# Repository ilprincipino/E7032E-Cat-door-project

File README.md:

# E7032E-Cat-door-project
Universal low power antennas for pet microchips
<p>
  
**Project members:** <br>
Matilda Segerlund, matseg-9@student.ltu.se  <br>
Nebez Rashid, nabras-9@student.ltu.se <br>
Anders Hagström, hagane-9@student.ltu.se <br>
Agnes Lindsten, agelin-7@student.ltu.se <br>
Arvid Mattsson, arvmat-9@student.ltu.se <br>
Jakob Ekvall, jakekv-9@student.ltu.se <br>

Link to report: [https://www.overleaf.com/read/vsyjcxfwmcch](https://www.overleaf.com/read/vsyjcxfwmcch) <br>

Link to presentation: https://docs.google.com/presentation/d/12QPiXXhClUaFdsH-6-YMc6YWno67U1GOmlV3GwxZOh8/edit?usp=sharing

Link to WBS/project plan: https://docs.google.com/spreadsheets/d/1j_RC8x2nzi24WwkHtlm5jIMLNItzt1e427vKWdE4rbc/edit?usp=sharing <br>

**Background:** <br>
Since the mid-80's, microchip implants have been used in pets and livestocks to identify them. These implements are a little larger than a rice grain. They are passive RFID chips that must be remotely powered to receive the identification information. They are progressively been required by law. <br>

Beside legal identification, these microchips can be used to identify a pet when they want to be fed (i.e., not allow an obese pet to over eat) or to let them enter or exit their home. The latter prevents "foreign" cats to enter homes where they have no business to be in. <br>

There is a problem when the orientation of the scanner's antenna and the microchips are not aligned. The pet doors and feeders are battery powered and fixed. The former results in not enough power to retrieve the information, while the latter could have been a solution by rotating the antenna (or chip inside the pet). <br>

**Objective:** <br>
The project is simply to design a low power antenna that allows the microchip to be read whatever is its relative orientation. <br>

**Key features:** <br>
* **Compatibility:** The solution must be ISO 11784 and ISO 11785 compliant. That is, it must be able to be optimized for 134.2 kHz, but should also be able to read at 125 kHz for US microchips.
* **Low power:** The cat door should work 6 months on four AA batteries.
* **Size:** It should fit in a pet door.
* **Temperature:** It should function in temperatures from -20°C to 60°C.
* **Internet ready:** The solution should be able to integrate a secured solution that connects to the Internet. This could include near field communication (NFC), bluetooth, and WiFi solutions. 

</p>

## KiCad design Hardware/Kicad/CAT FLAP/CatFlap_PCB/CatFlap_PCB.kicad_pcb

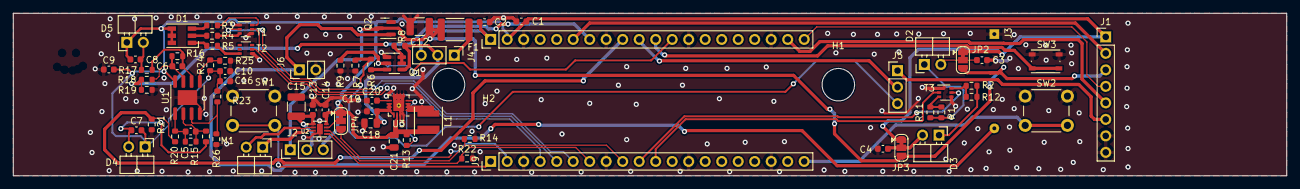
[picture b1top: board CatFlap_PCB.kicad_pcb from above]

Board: 2 copper layers, 196.0 x 25.0 mm, 77 parts (0 on the bottom side), 56 nets.

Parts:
C1, C2, C10, C13, C14, C16, C19: 100n; C_0603_1608Metric
C3, C4, C9: 1u; C_0603_1608Metric
C5, C6, C7, C8: 1.4p; C_0603_1608Metric
C12, C15: 100u; C_1210_3225Metric
C18: 10u; C_0805_2012Metric
C20: 3.3n; C_0603_1608Metric
C21: 22u; C_0805_2012Metric
D1: LED_RGB; LED_RGB_PLCC-6
D2, D3: IR-LED; PinHeader_1x02_P2.54mm_Horizontal
D4, D5: LED; PinHeader_1x02_P2.54mm_Horizontal
F1: Polyfuse; Fuse_1812_4532Metric
H1, H2: MountingHole; MountingHole_5mm
J1: Conn_01x08; PinHeader_1x08_P2.54mm_Vertical
J2, J5: Conn_01x03; PinHeader_1x03_P2.54mm_Vertical
J3: Battery pack; BatteryHolder_MPD_BH-18650-PC2
J4: Conn_01x03_Socket; PinHeader_1x03_P2.54mm_Vertical
J6: Conn_01x02; PinHeader_1x02_P2.54mm_Vertical
J8, J9: Conn_01x20; PinHeader_1x20_P2.54mm_Vertical
JP2, JP3, JP4: SolderJumper_3_Bridged12; SolderJumper-3_P1.3mm_Bridged12_RoundedPad1.0x1.5mm
L1: 2.2u; L_Coilcraft_XxL4020
M1: Motor_DC; PinHeader_1x02_P2.54mm_Horizontal
Q1: NX3008CBKS; TSOT-23-6
Q2: Q_PMOS_DGS; SOT-23
R1, R2, R11, R12: 6.8; R_0603_1608Metric
R3: 68; R_0603_1608Metric
R4: 22; R_0603_1608Metric
R5: 10; R_0603_1608Metric
R6: 330k; R_0603_1608Metric
R7: 220k; R_0603_1608Metric
R8, R9: 1meg; R_0603_1608Metric
R10, R17, R18, R19, R20, R21: 0; R_0603_1608Metric
R13, R14, R15, R16, R22, R23, R24, R25, R26: 100k; R_0603_1608Metric
SW1, SW2: SW_Push; SW_PUSH_6mm_H4.3mm
SW3: SW_Push; SW_Push_1P1T_NO_Vertical_Wuerth_434133025816
T1, T2, T3: NX3008NBKS; SOT-363_SC-70-6
U1: LM358_DFN; SOIC-8-1EP_3.9x4.9mm_P1.27mm_EP2.29x3mm
U2: DRV8837DSGR; SON50P200X200X80-9N
U3: TPS62132; VQFN-16-1EP_3x3mm_P0.5mm_EP1.68x1.68mm_ThermalVias

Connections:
+3.3V: C1.2, C7.2, C8.2, C9.2, C10.2, C14.2, C16.2, C21.2, D1.4 (BA), D1.5 (GA), D1.6 (RA), D4.1 (K), D5.1 (K), J1.1, J2.3, J8.2, JP2.1 (A), JP3.1 (A), JP4.1 (A), L1.2, R13.2, R23.1, R24.1, U1.8 (V+), U2.8 (VCC), U3.14 (VOS)
/GP27_A0: J5.2, J8.10
ADC_VREF_Antenn: J1.2, J8.6
Antenn_Analog: J1.6, J5.1
Antenn_Digital_1: J1.4, J8.20
Antenn_Digital_2: J1.5, J8.19
BAT_MON: J5.3, R6.2, R7.1
BAT_MON_EN: J8.12, Q1.2 (G), R9.1
Cat+: J9.20, SW2.2
GND: C1.1, C2.1, C3.1, C4.1, C9.1, C10.1, C12.1, C13.1, C14.1, C15.1, C16.1, C18.1, C19.1, C20.2, C21.1, J1.7, J1.8, J3.1 (GND), J6.2, J8.3, J8.8, J8.13, J8.18, J9.3, J9.8, J9.13, J9.18, Q1.1 (S), Q2.2 (G), R7.2, R9.2, R14.2, R19.2, R21.2, R22.1, R25.2, R26.1, SW1.1, SW2.1, SW3.1, T1.1, T1.4, T2.1, T3.1, T3.4, U1.4 (V-), U1.9 (PAD), U2.4 (GND), U2.9 (EXP), U3.5 (FB), U3.6 (AGND), U3.7 (FSW), U3.8 (DEF), U3.15 (PGND), U3.16 (PGND), U3.17 (EP)
Gear: J9.1, SW1.2
IR_R_INSIDE: J8.9, R20.1, R21.1
IR_R_OUTSIDE: J8.7, R18.1, R19.1
IR_T_INSIDE: J9.11, T3.2
IR_T_OUTSIDE: J9.10, T3.5
LED_B: J9.4, T2.2
LED_G: J9.5, T1.5
LED_R: J9.6, T1.2
M_LOCK: J9.9, R14.1, U2.6 (IN1)
M_SLEEP: J9.2, JP4.3 (B)
M_UNLOCK: J9.7, R22.2, U2.5 (IN2)
unnamed: C5.1, R15.1, R20.2, U1.1
unnamed: C6.1, R16.1, R18.2, U1.7
unnamed: D1.3 (BK), R3.2
unnamed: D1.2 (GK), R4.2
unnamed: D1.1 (RK), R5.2
unnamed: C3.2, D2.2 (A), JP2.2 (C)
unnamed: D2.1 (K), R1.2, R11.2
unnamed: C4.2, D3.2 (A), JP3.2 (C)
unnamed: D3.1 (K), R2.2, R12.2
unnamed: C7.1, D4.2 (A), R10.2
unnamed: C8.1, D5.2 (A), R17.2
unnamed: C13.2, C15.2, J2.2, U2.1 (VM)
unnamed: J3.2 (V+), J6.1, Q2.1 (D)
unnamed: F1.1, J4.1
unnamed: JP4.2 (C), U2.7 (~SLEEP)
unnamed: L1.1, U3.1 (SW), U3.2 (SW), U3.3 (SW)
unnamed: M1.1 (+), U2.3 (OUT2)
unnamed: M1.2 (-), U2.2 (OUT1)
unnamed: Q1.5 (G), Q1.6 (D), R8.2
unnamed: Q1.3 (D), R6.1
unnamed: R1.1, R11.1, T3.3
unnamed: R3.1, T1.6
unnamed: R4.1, T1.3
unnamed: R5.1, T2.6
unnamed: R2.1, R12.1, T3.6
unnamed: R23.2, R26.2, U1.3 (+)
unnamed: C5.2, R10.1, R15.2, U1.2 (-)
unnamed: R24.2, R25.1, U1.5 (+)
unnamed: C6.2, R16.2, R17.1, U1.6 (-)
unnamed: R13.1, U3.4 (PG)
unnamed: C20.1, U3.9 (SS/TR)
Reset: J8.11, SW3.2
VBUS: C2.2, J4.3, J8.1
VDD: C12.2, F1.2, J1.3, J2.1, JP2.3 (B), JP3.3 (B), Q2.3 (S)
V_BAT: C18.2, C19.2, J4.2, Q1.4 (S), R8.1, U3.10 (AVIN), U3.11 (PVIN), U3.12 (PVIN), U3.13 (EN)

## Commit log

2023-08-28 Create Meeting 0
2023-08-30 Create Meeting 1
2023-09-01 Update Meeting 1
2023-09-05 Create sources
2023-09-05 Create Inköpslista
2023-09-05 Update sources
2023-09-05 Update Inköpslista
2023-09-06 Create Meeting with Johan
2023-09-09 Create Datasheets folder
2023-09-09 Delete Datasheets
    Messed up, woops xD
2023-09-09 Create URL-for-Datasheets
2023-09-09 Added Datasheets for IR-transmitter and receiver.
2023-09-10 Update sources about motor control.
2023-09-10 Create Notes for potential ideas.
2023-09-12 Create Matilda
2023-09-12 Create Anders
2023-09-12 Create Agnes
2023-09-12 Create Nebez
2023-09-12 Create Jakob
2023-09-12 Create Arvid
2023-09-12 Update Arvid
2023-09-12 Create Motor
2023-09-12 Added arduino code for h-bro V1
2023-09-13 Update Notes
2023-09-14 Added Datasheet for H-Bridge IC
2023-09-14 Create Oscilloscope files of RFID tags
2023-09-14 Create s
2023-09-14 Added files for test with Johan 2023-09-13
2023-09-15 Update Matilda
2023-09-15 Update Anders for week 37
2023-09-17 Update Nebez
2023-09-17 Update Jakob
2023-09-19 Update Anders
2023-09-19 Update URL-for-Datasheets
2023-09-19 Create Hardware folder for Kicad files and Notes etc
2023-09-19 Added Kicad folder and included old mouse project
2023-09-19 I messed up again and again
2023-09-19 Added kicadfolder and cat flap and some old soluti
2023-09-19 Cleaned up CAT FLAP folder for future kicad files
2023-09-19 I messed up again, but now it worked :cheers:
2023-09-20 Update Agnes
2023-09-21 Create Class diagram in text
2023-09-24 Update Nabaz
2023-09-26 Create ResultNotes to be able to write result to see progress
2023-09-26 Update ResultNotes
2023-09-27 Delete Software/Add_cat.py
    Not needed anymore
2023-09-28 Python code for motor
    Will have to change input from buttons to antenna, and make sure motor works (not with LEDs)
2023-10-02 Create fillerdoc
2023-10-02 Overleaf link
2023-10-02 Updated Powermanagement
2023-10-05 Create App functionality
2023-10-05 How to save the pi
2023-10-10 Some things approved
2023-10-10 Update App functionality
2023-10-11 First draft
2023-10-11 Another one!
2023-10-12 Create catflap
2023-10-15 Rename Nabaz
2023-10-15 Nabaz
2023-10-23 Added iso files
2023-10-23 EM4100 protocol
2023-10-23 Update sources with FDX-B and HDX
2023-10-23 EM4005/EM4105 FDX-B datasheet
2023-10-31 Create App frontend
2023-11-06 Added catapp_2 (frontend) directory
